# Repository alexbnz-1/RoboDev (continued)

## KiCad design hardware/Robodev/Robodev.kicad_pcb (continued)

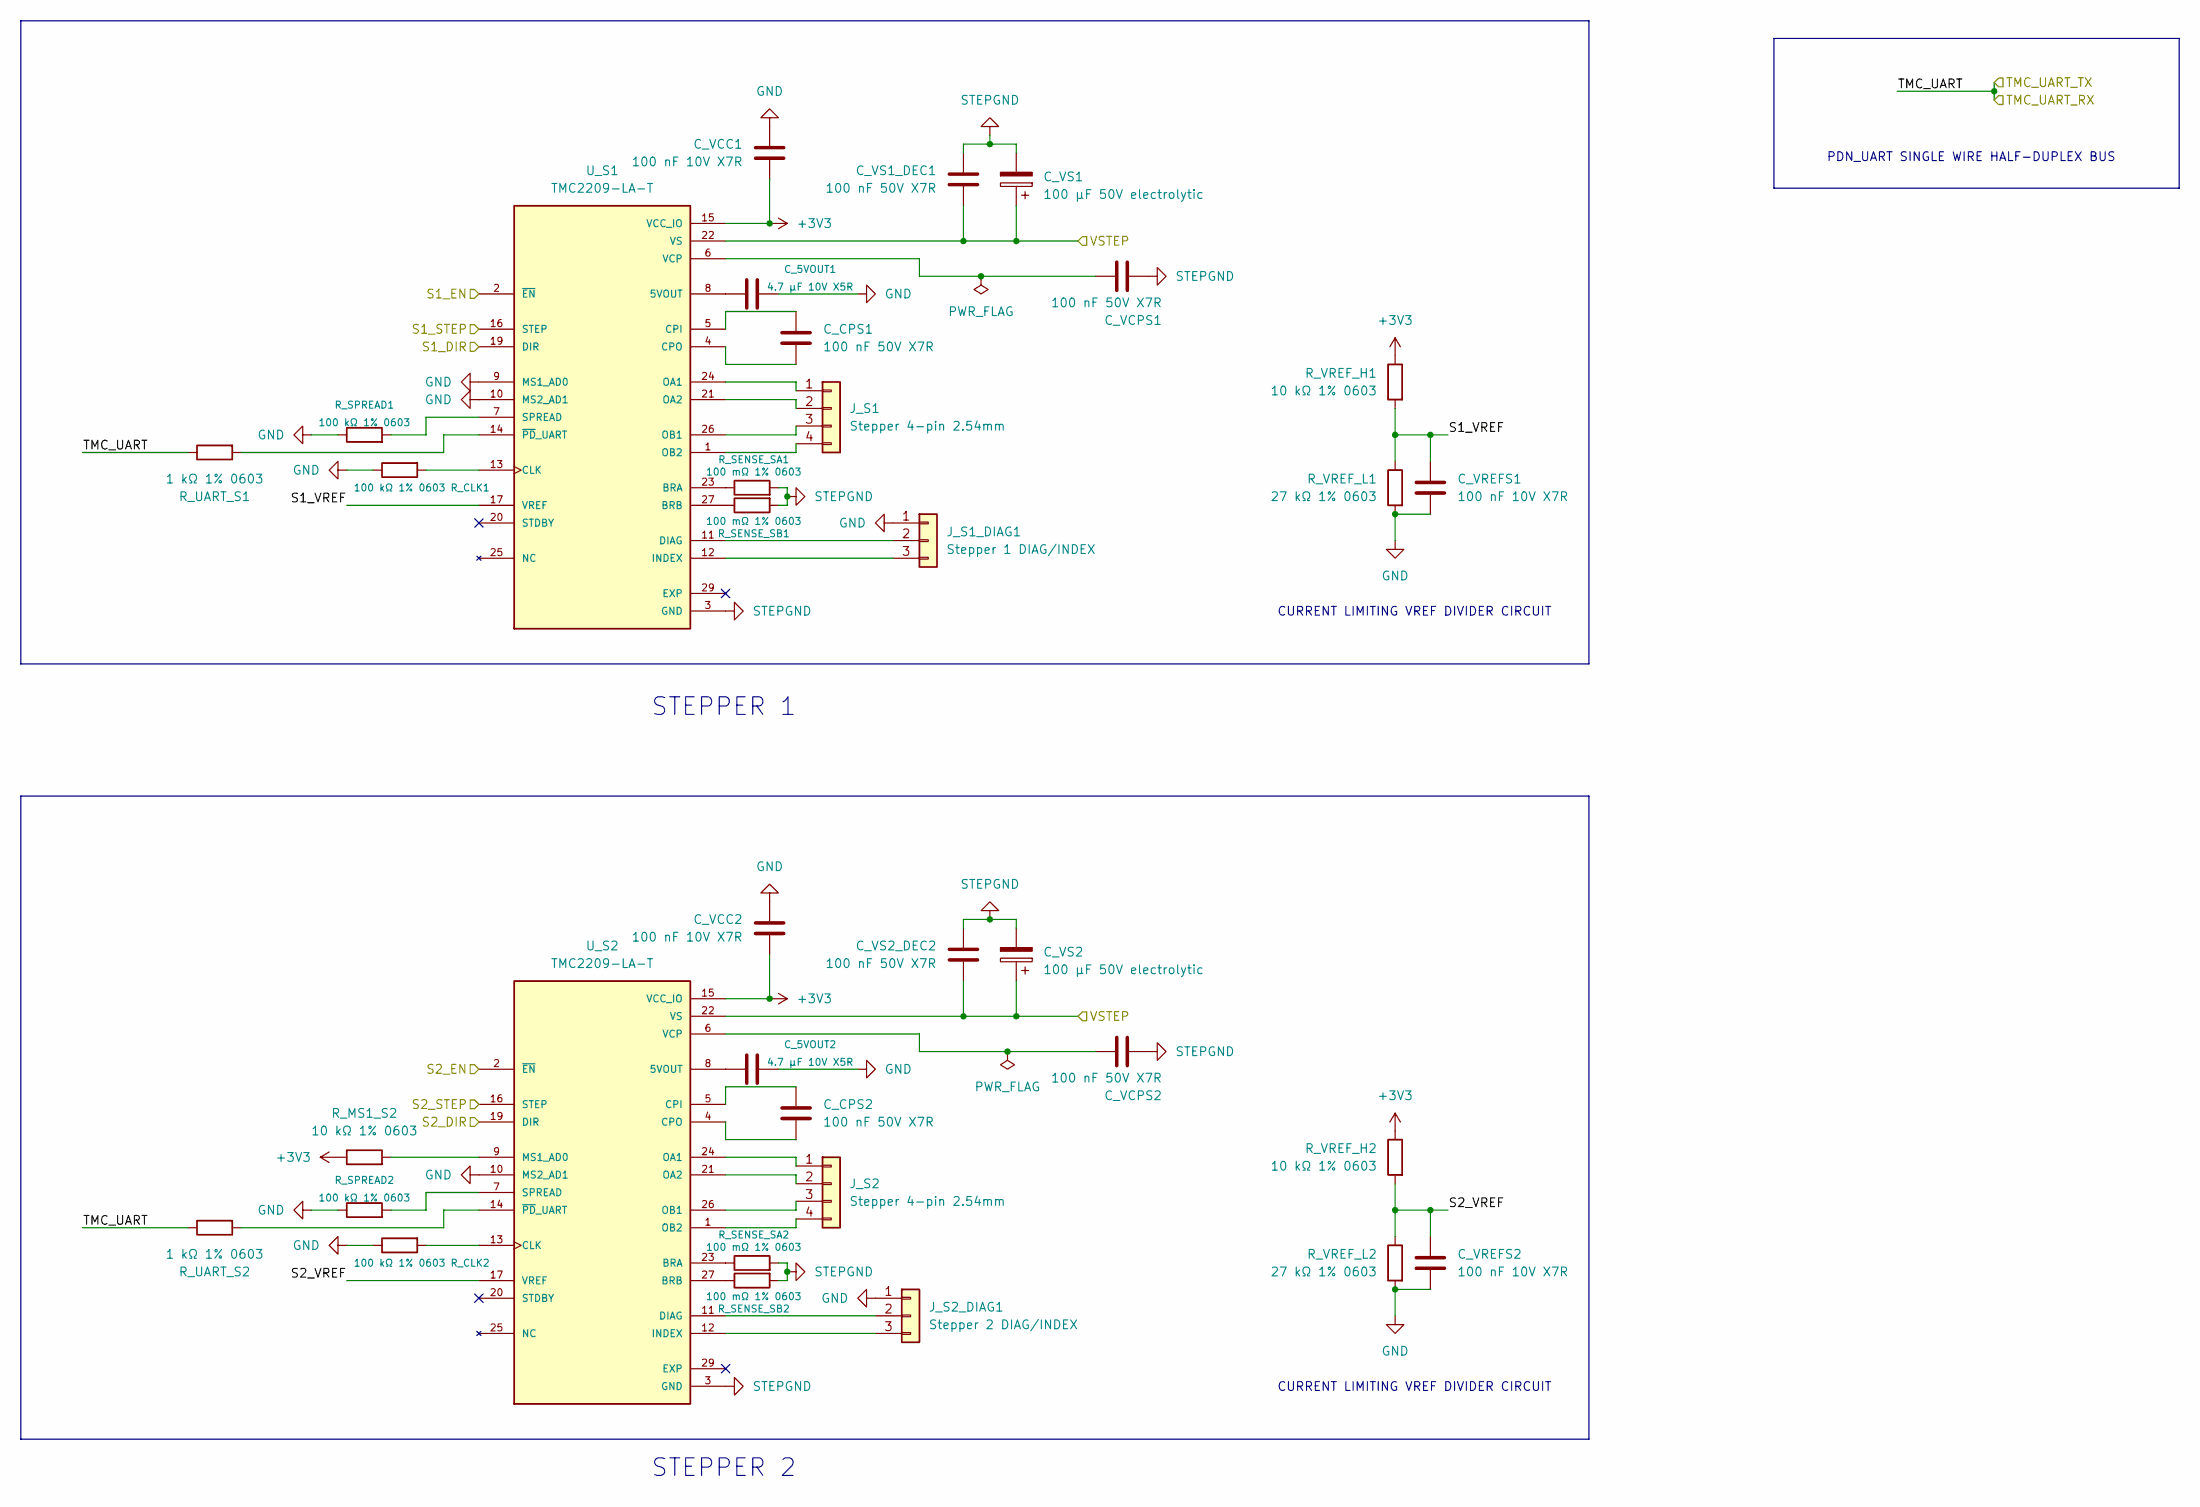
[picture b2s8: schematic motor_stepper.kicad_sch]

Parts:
C_5VOUT1, C_5VOUT2: 4.7 µF 10V X5R; C_0603_1608Metric
C_CPS1, C_CPS2: 100 nF 50V X7R; C_0603_1608Metric
C_VCC1, C_VCC2: 100 nF 10V X7R; C_0603_1608Metric
C_VCPS1, C_VCPS2: 100 nF 50V X7R; C_0603_1608Metric
C_VREFS1, C_VREFS2: 100 nF 10V X7R; C_0603_1608Metric
C_VS1, C_VS2: 100 µF 50V electrolytic; CP_Radial_D8.0mm_P3.50mm
C_VS1_DEC1, C_VS2_DEC2: 100 nF 50V X7R; C_0603_1608Metric
J_S1, J_S2: Stepper 4-pin 2.54mm; PinHeader_1x04_P2.54mm_Vertical
J_S1_DIAG1: Stepper 1 DIAG/INDEX; PinHeader_1x03_P2.54mm_Vertical
J_S2_DIAG1: Stepper 2 DIAG/INDEX; PinHeader_1x03_P2.54mm_Vertical
R_CLK1, R_CLK2: 100 kΩ 1% 0603; R_0603_1608Metric
R_MS1_S2: 10 kΩ 1% 0603; R_0603_1608Metric
R_SENSE_SA1, R_SENSE_SA2: 100 mΩ 1% 0603; R_0603_1608Metric
R_SENSE_SB1, R_SENSE_SB2: 100 mΩ 1% 0603; R_0603_1608Metric
R_SPREAD1, R_SPREAD2: 100 kΩ 1% 0603; R_0603_1608Metric
R_UART_S1, R_UART_S2: 1 kΩ 1% 0603; R_0603_1608Metric
R_VREF_H1, R_VREF_H2: 10 kΩ 1% 0603; R_0603_1608Metric
R_VREF_L1, R_VREF_L2: 27 kΩ 1% 0603; R_0603_1608Metric
U_S1, U_S2: TMC2209-LA-T; QFN50P500X500X90-29N; PARTREV 1.09

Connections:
+3V3: C_VCC1.2, C_VCC2.2, R_MS1_S2.1, R_VREF_H1.1, R_VREF_H2.1, U_S1.15 (VCC_IO), U_S2.15 (VCC_IO); also elsewhere on the board
/motor_stepper/S1_DIR: U_S1.19 (DIR); also elsewhere on the board
/motor_stepper/S1_STEP: U_S1.16 (STEP); also elsewhere on the board
/motor_stepper/S1_VREF: C_VREFS1.1, R_VREF_H1.2, R_VREF_L1.1, U_S1.17 (VREF)
/motor_stepper/S2_DIR: U_S2.19 (DIR); also elsewhere on the board
/motor_stepper/S2_STEP: U_S2.16 (STEP); also elsewhere on the board
/motor_stepper/S2_VREF: C_VREFS2.1, R_VREF_H2.2, R_VREF_L2.1, U_S2.17 (VREF)
/motor_stepper/TMC_UART: R_UART_S1.1, R_UART_S2.1; also elsewhere on the board
/stm32/S1_EN: U_S1.2 (~EN); also elsewhere on the board
/stm32/S2_EN: U_S2.2 (~EN); also elsewhere on the board
GND: C_5VOUT1.2, C_5VOUT2.2, C_VCC1.1, C_VCC2.1, C_VREFS1.2, C_VREFS2.2, J_S1_DIAG1.1, J_S2_DIAG1.1, R_CLK1.1, R_CLK2.1, R_SPREAD1.1, R_SPREAD2.1, R_VREF_L1.2, R_VREF_L2.2, U_S1.9 (MS1_AD0), U_S1.10 (MS2_AD1), U_S2.10 (MS2_AD1); also elsewhere on the board
unnamed: J_S1.1, U_S1.24 (OA1)
unnamed: J_S1.2, U_S1.21 (OA2)
unnamed: J_S1.3, U_S1.26 (OB1)
unnamed: J_S1.4, U_S1.1 (OB2)
unnamed: J_S1_DIAG1.2, U_S1.11 (DIAG)
unnamed: J_S1_DIAG1.3, U_S1.12 (INDEX)
unnamed: J_S2.1, U_S2.24 (OA1)
unnamed: J_S2.2, U_S2.21 (OA2)
unnamed: J_S2.3, U_S2.26 (OB1)
unnamed: J_S2.4, U_S2.1 (OB2)
unnamed: J_S2_DIAG1.2, U_S2.11 (DIAG)
unnamed: J_S2_DIAG1.3, U_S2.12 (INDEX)
unnamed: C_5VOUT1.1, U_S1.8 (5VOUT)
unnamed: R_SENSE_SA1.1, U_S1.23 (BRA)
unnamed: R_SENSE_SB1.1, U_S1.27 (BRB)
unnamed: R_CLK1.2, U_S1.13 (CLK)
unnamed: C_CPS1.1, U_S1.5 (CPI)
unnamed: C_CPS1.2, U_S1.4 (CPO)
unnamed: R_SPREAD1.2, U_S1.7 (SPREAD)
unnamed: C_VCPS1.1, U_S1.6 (VCP)
unnamed: R_UART_S1.2, U_S1.14 (~PD_UART)
unnamed: C_5VOUT2.1, U_S2.8 (5VOUT)
unnamed: R_SENSE_SA2.1, U_S2.23 (BRA)
unnamed: R_SENSE_SB2.1, U_S2.27 (BRB)
unnamed: R_CLK2.2, U_S2.13 (CLK)
unnamed: C_CPS2.1, U_S2.5 (CPI)
unnamed: C_CPS2.2, U_S2.4 (CPO)
unnamed: R_MS1_S2.2, U_S2.9 (MS1_AD0)
unnamed: R_SPREAD2.2, U_S2.7 (SPREAD)
unnamed: C_VCPS2.1, U_S2.6 (VCP)
unnamed: R_UART_S2.2, U_S2.14 (~PD_UART)
STEPGND: C_VCPS1.2, C_VCPS2.2, C_VS1.2, C_VS1_DEC1.1, C_VS2.2, C_VS2_DEC2.1, R_SENSE_SA1.2, R_SENSE_SA2.2, R_SENSE_SB1.2, R_SENSE_SB2.2, U_S1.3 (GND), U_S2.3 (GND); also elsewhere on the board
VS: C_VS1.1, C_VS1_DEC1.2, C_VS2.1, C_VS2_DEC2.2, U_S1.22 (VS), U_S1.28 (VS), U_S2.22 (VS), U_S2.28 (VS); also elsewhere on the board

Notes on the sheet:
CURRENT LIMITING VREF DIVIDER CIRCUIT
STEPPER 1
PDN_UART SINGLE WIRE HALF-DUPLEX BUS
STEPPER 2

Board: 4 copper layers, 258 parts (109 on the bottom side), 237 nets, no tracks yet.

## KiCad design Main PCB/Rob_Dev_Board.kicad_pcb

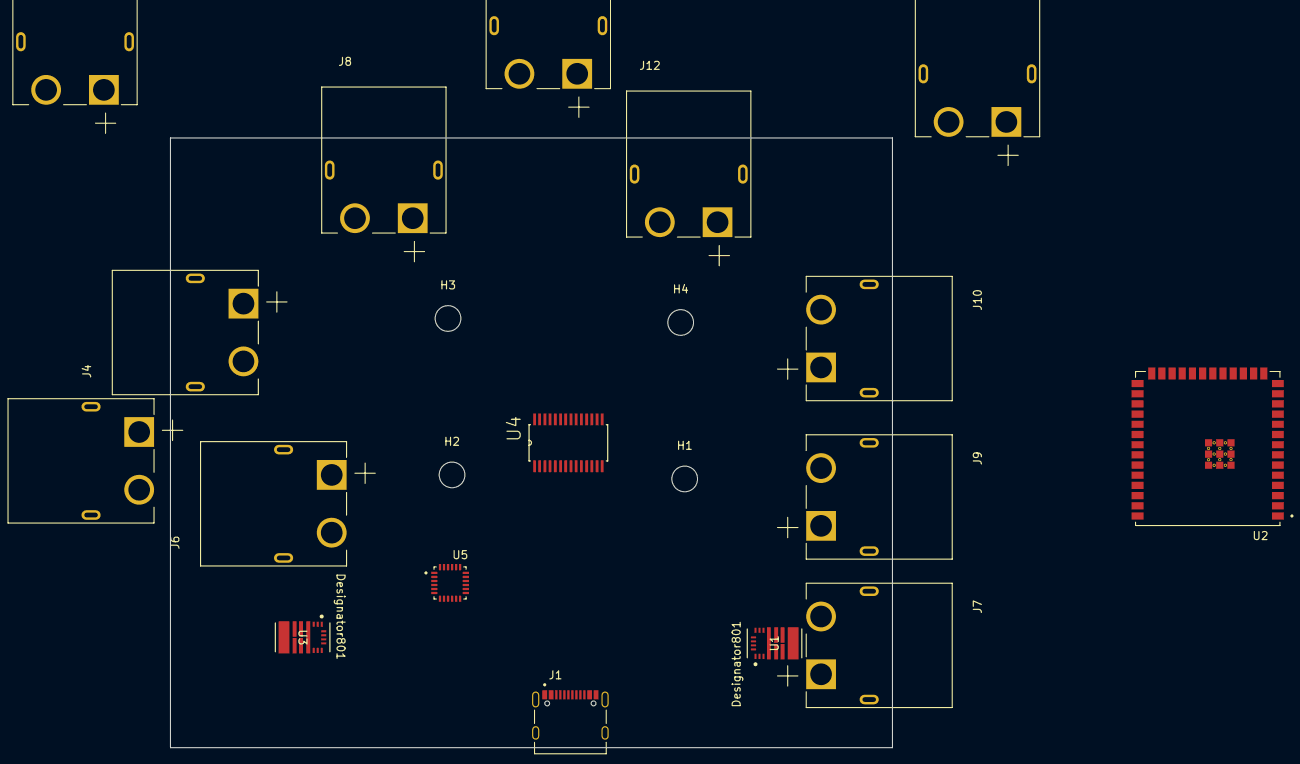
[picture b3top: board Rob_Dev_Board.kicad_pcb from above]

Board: 4 copper layers, 90.0 x 76.0 mm, 21 parts (0 on the bottom side), 4 nets, no tracks yet.

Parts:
H1, H2, H3, H4: MountingHole; MountingHole_3.2mm_M3
J1: TYPE-C-31-M-12; HRO_TYPE-C-31-M-12
J2, J3, J4, J5, J6, J7, J8, J9, J10, J11, J12: XT60PW-M; AMASS_XT60PW-M
U1, U3: DRV8245HQRXZRQ1; RXZ0016A-MFG
U2: ESP32-S3-WROOM-1U-N16R8; XCVR_ESP32-S3-WROOM-1U-N16R8
U4: PCA9685PW_118; SOP65P640X110-28N
U5: MPU-6050; QFN50P400X400X95-24N

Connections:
unnamed: J1.A1_B12 (GND), J1.B1_A12 (GND)
unnamed: J1.S1 (SHIELD), J1.S2 (SHIELD), J1.S3 (SHIELD), J1.S4 (SHIELD)
unnamed: J1.A4_B9 (VBUS), J1.B4_A9 (VBUS)
unnamed: U5.2 (NC), U5.3 (NC), U5.4 (NC), U5.5 (NC), U5.14 (NC), U5.15 (NC), U5.16 (NC), U5.17 (NC)

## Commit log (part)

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2025-10-23 Added PCB project files
2025-10-23 Added technical docs for ESP32-S3
2025-10-23 Added DRV8245H datasheet
2025-10-24 Added component files for ESP32 and DRV8245H motor driver
2025-11-05 Changed components for ESP32 and motor driver to in stock options from supplier
2025-11-05 Added some more components to PCB design, added datasheet for possible BLDC motor driver
2025-11-05 Changed structure of project to allow for BLDC drivers
2025-11-06 Added acceler. and connector type to part library
2025-11-27 Testing
2025-11-27 jawndice
2025-11-27 more testing
2025-11-27 test
2025-11-27 testing more
2026-04-04 First major progress made towards planning. Pin layout drafted, no power systems yet.
2026-05-24 Substantial changes made - See readme for current running status
2026-05-24 Updated documentation to reflect changes
2026-05-24 Add MIT License to the project
2026-05-24 Add CONTRIBUTING.md for project guidelines
2026-05-24 Removed artifacts of kicad and updated contributing.md
